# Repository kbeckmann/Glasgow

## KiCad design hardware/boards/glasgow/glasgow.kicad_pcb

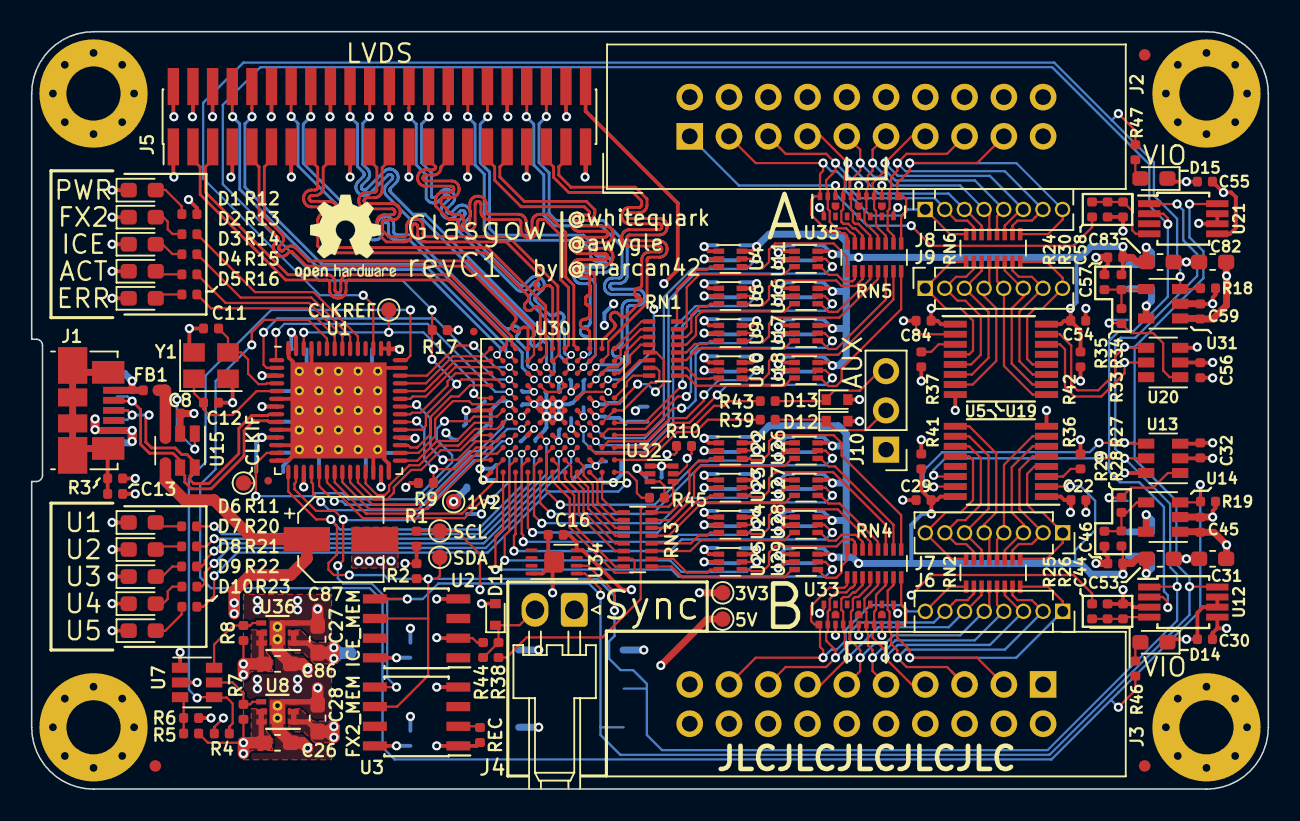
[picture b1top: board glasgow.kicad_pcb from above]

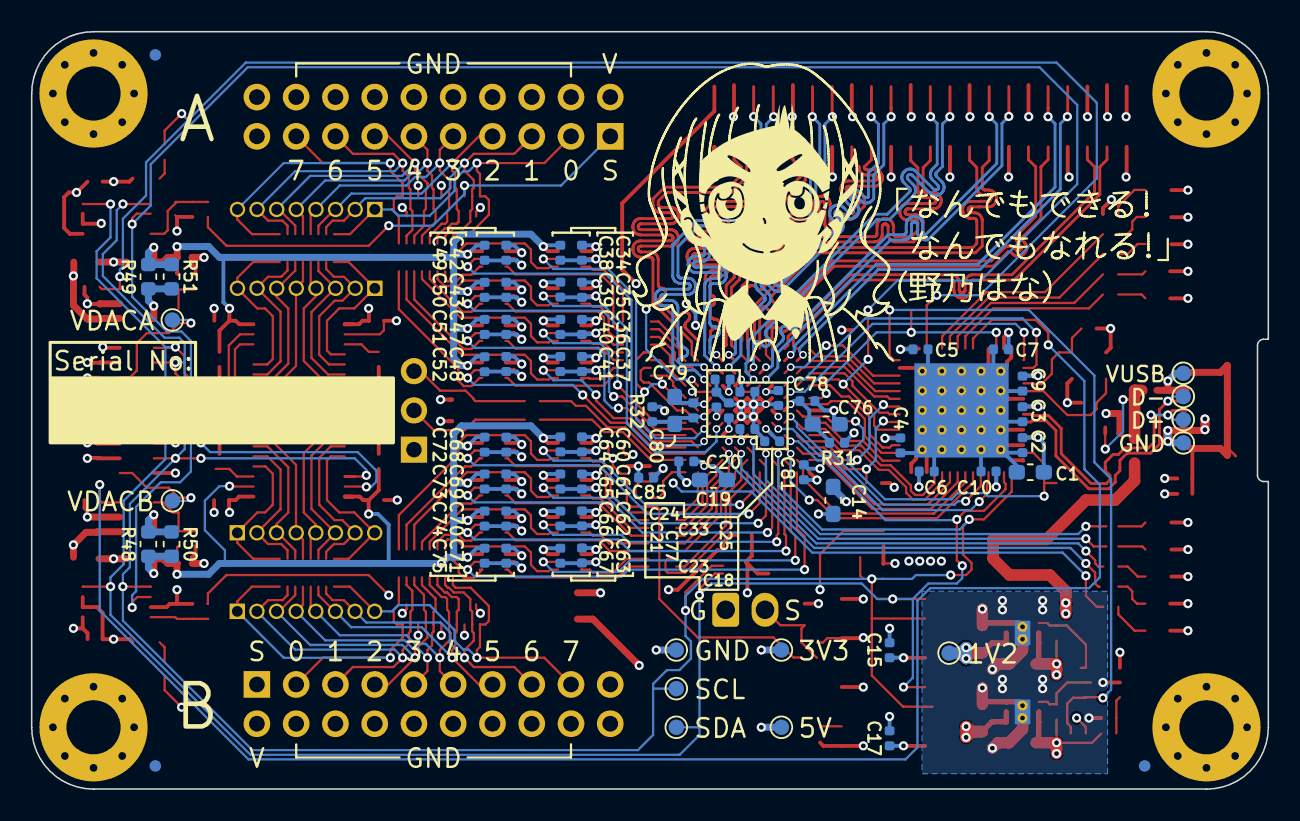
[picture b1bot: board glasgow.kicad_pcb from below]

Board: 4 copper layers, 80.0 x 49.0 mm, 239 parts (81 on the bottom side), 214 nets.

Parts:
C1, C14, C19, C26, C27, C28, C31, C53, C76, C80, C82, C83, C86: 4u7; C_0603_1608Metric_Pad1.05x0.95mm_HandSolder
C2, C3, C4, C5, C6, C7, C8, C9, C10, C13, C15, C16, C17, C18, C20, C21, C22, C23, C24, C25, C29, C30, C32, C33, C34, C35, C36, C37, C38, C39, C40, C41, C42, C43, C45, C46, C47, C48, C49, C50, C51, C52, C54, C55, C56, C57, C59, C60, C61, C62, C63, C64, C65, C66, C67, C68, C69, C70, C71, C72, C73, C74, C75, C77, C78, C79, C81, C84, C85: u1; C_0402_1005Metric
C11, C12: 18p; C_0402_1005Metric
C44, C58: 12n; C_0402_1005Metric
C87: 150u; CP_Elec_5x3.9
D1, D2, D3, D14, D15: GRN; LED_0603_1608Metric_Pad1.05x0.95mm_HandSolder
D4: YEL; LED_0603_1608Metric_Pad1.05x0.95mm_HandSolder
D5: RED; LED_0603_1608Metric_Pad1.05x0.95mm_HandSolder
D6, D10: BLU; LED_0603_1608Metric_Pad1.05x0.95mm_HandSolder
D7, D9: PNK; LED_0603_1608Metric_Pad1.05x0.95mm_HandSolder
D8: WHT; LED_0603_1608Metric_Pad1.05x0.95mm_HandSolder
D11, D12, D13: ESD5Z5.0T1G; D_SOD-523
FB1: Ferrite_Bead; L_0402_1005Metric
FID1, FID2, FID3, FID4, FID5, FID6: Fiducial_0.75mm_Dia_1.5mm_Outer
FID7, FID8: Fiducial_0.5mm_Dia_1mm_Outer
J1: USB_B_Micro; USB_Micro-B_Molex_47346-0001
J2, J3: Conn_02x10_Odd_Even; IDC-Header_2x10_P2.54mm_Vertical
J4: Conn_01x02; Molex_KK-254_1x02_P2.54mm_Horizontal
J5: Conn_02x22_Odd_Even; PinHeader_2x22_P1.27mm_Vertical_SMD
J6, J7, J8, J9: Conn_01x08; PinSocket_1x08_P1.27mm_Vertical
J10: Conn_01x03; PinHeader_1x03_P2.54mm_Vertical
MK1, MK2, MK3, MK4: Mounting_Hole_PAD; MountingHole_3.5mm_Pad_Via_CrtYd
NONO_HANA: MECHOKKU; nono_hana
R1, R2, R15: 2k2; R_0402_1005Metric
R3, R4, R7, R8, R9, R17: 100k; R_0402_1005Metric
R5, R29, R35: 24k3; R_0402_1005Metric
R6, R16, R18, R19, R20, R22, R24, R25, R26, R30, R36, R37, R44: 10k; R_0402_1005Metric
R10, R41, R42: 1k; R_0402_1005Metric
R11, R23: 4k7; R_0402_1005Metric
R12, R13, R14, R46, R47: 20k; R_0402_1005Metric
R21: 6k8; R_0402_1005Metric
R27, R33: 49k9; R_0402_1005Metric
R28, R34: 59k; R_0402_1005Metric
R31, R32: 100; R_0402_1005Metric
R38, R39, R43, R45: 47; R_0402_1005Metric
R40: DNP; R_0402_1005Metric
R48, R49: 0.68; R_0603_1608Metric
R50, R51: DNP; R_0603_1608Metric
RN1, RN3, RN4, RN5: 33; R_Array_Convex_8x0602
RN2, RN6: 10k; R_Array_Convex_8x0602
TP1, TP8: 5V; TestPoint_Pad_D1.0mm
TP2, TP17: 1V2; TestPoint_Pad_D1.0mm
TP3, TP7, TP9: 3V3; TestPoint_Pad_D1.0mm
TP4, TP10: SDA; TestPoint_Pad_D1.0mm
TP5, TP11: SCL; TestPoint_Pad_D1.0mm
TP6: CLKREF; TestPoint_Pad_D1.0mm
TP12: GND; TestPoint_Pad_D1.0mm
TP13: VBUS; TestPoint_Pad_D1.0mm
TP14: USBGND; TestPoint_Pad_D1.0mm
TP15: USBDP; TestPoint_Pad_D1.0mm
TP16: USBDM; TestPoint_Pad_D1.0mm
TP18, TP19: VDAC; TestPoint_Pad_D1.0mm
U1: CY7C68013A-56LTX; Cypress_QFN-56-1EP_8x8mm_P0.5mm_EP6.22x6.22mm_ThermalVias
U2: CAT24M01W; SOIC-8_3.9x4.9mm_P1.27mm
U3: CAT24C256W; SOIC-8_3.9x4.9mm_P1.27mm
U4, U6, U9, U10, U11, U16, U17, U18, U22, U23, U24, U25, U26, U27, U28, U29, U32: SN74LVC1T45DRL; SOT-563
U5, U19: PCA6408APW; TSSOP-16_4.4x5mm_P0.65mm
U7: LM3880MF-1AF; SOT-23-6
U8: TLV75533PDRVR; DFN-6-1EP_2x2mm_P0.65mm_EP1x1.6mm_ThermalVias
U12, U21: ADC081C021CIMM; MSOP-8_3x3mm_P0.65mm
U13, U20: DAC081C081CIMK; SOT-23-6
U14, U31: TPS73101DBV; SOT-23-5
U15: TPD3S014; SOT-23-6
U30: ICE40HX8K-BG121; BGA-121_9.0x9.0mm_Layout11x11_P0.8mm_Ball0.4mm_Pad0.35mm_NS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
U33, U35: MG2040; UDFN-18-3EP_5.5x1.5mm_P0.5mm_EP0.5x0.5mm
U34: ATECC508A; WDFN-8-1EP_3x2mm_P0.5mm_EP1.3x1.4mm
U36: TLV73312PQDRVRQ1; DFN-6-1EP_2x2mm_P0.65mm_EP1x1.6mm_ThermalVias
Y1: 24M; Crystal_SMD_3225-4Pin_3.2x2.5mm

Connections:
+1V2: C14.1, C18.1, C24.1, C25.1, C27.1, C77.1, R31.2, R32.2, TP2.1, TP17.1, U30.D4, U30.D8, U30.H4, U30.H8, U36.1, U36.2
+3V3: C1.1, C2.1, C3.1, C4.1, C5.1, C6.1, C7.1, C9.1, C10.1, C15.1, C16.1, C17.1, C19.1, C20.1, C21.1, C22.1, C23.1, C28.1, C30.1, C32.1, C34.1, C35.1, C36.1, C37.1, C42.1, C43.1, C47.1, C48.1, C55.1, C56.1, C60.1, C61.1, C62.1, C63.1, C68.1, C69.1, C70.1, C71.1, C81.1, C84.1, C85.1, J5.2, R1.2, R2.2, R4.2, R12.1, R17.2, R36.2, R37.2, R40.2, R44.2, TP3.1, TP9.1, U1.3, U1.7, U1.11, U1.17, U1.27, U1.32, U1.43, U1.44, U1.55, U2.2, U2.8, U3.1, U3.8, U4.1, U5.1, U6.1, U8.1, U8.2, U9.1, U10.1, U11.1, U12.5, U13.2, U16.1, U17.1, U18.1, U19.1, U20.2, U21.5, U22.1, U23.1, U24.1, U25.1, U26.1, U27.1, U28.1, U29.1, U30.C10, U30.D6, U30.F8, U30.H6, U30.L11, U32.1, U32.6, U34.8
+5V: C26.2, C31.1, C45.1, C59.1, C82.1, C86.2, C87.1, R5.2, R7.2, R8.2, TP1.1, TP8.1, U7.1, U8.5, U8.6, U14.1, U15.4, U31.1, U36.5, U36.6
/1V2EN: R8.1, U7.6, U36.4
/3V3EN: R7.1, U7.5, U8.4
/A0: U1.37, U30.K3
/A1: U1.38, U30.L2
/CLKIF: TP7.1, U1.13, U30.K6
/CLKREF: TP6.1, U1.54, U30.D5, U30.L5
/D0: U1.18, U30.H7
/D1: U1.19, U30.J7
/D2: U1.20, U30.J9
/D3: U1.21, U30.K10
/D4: U1.22, U30.L10
/D5: U1.23, U30.K9
/D6: U1.24, U30.L8
/D7: U1.25, U30.K7
/ENVA: R18.1, R47.1, U1.45, U31.3
/ENVB: R19.1, R46.1, U1.51, U14.3
/FLAGA: U1.29, U30.L7
/FLAGB: U1.30, U30.K5
/FLAGC: U1.31, U30.L4
/FLAGD: U1.40, U30.J3
/FPGA_DONE: U1.36, U30.K8
/GNDPLL0: C76.2, C78.2, U30.L6
/GNDPLL1: C79.2, C80.2, U30.C5
/IO_Banks/DA0: U4.5, U30.C7
/IO_Banks/DA1: U11.5, U30.C8
/IO_Banks/DA2: U6.5, U30.D7
/IO_Banks/DA3: U16.5, U30.A7
/IO_Banks/DA4: U9.5, U30.B8
/IO_Banks/DA5: U17.5, U30.A8
/IO_Banks/DA6: U10.5, U30.B9
/IO_Banks/DA7: U18.5, U30.A9
/IO_Banks/DB0: U22.5, U30.F9
/IO_Banks/DB1: U26.5, U30.G11
/IO_Banks/DB2: U23.5, U30.G10
/IO_Banks/DB3: U27.5, U30.H11
/IO_Banks/DB4: U24.5, U30.H10
/IO_Banks/DB5: U28.5, U30.J11
/IO_Banks/DB6: U25.5, U30.J10
/IO_Banks/DB7: U29.5, U30.K11
/IO_Banks/IO_Buffer_A/VFB: R33.2, R34.1, R35.2, U31.4
/IO_Banks/IO_Buffer_A/VSAMP: C58.1, R24.1, R30.2, U21.4
/IO_Banks/IO_Buffer_A/VSENSE: J2.1, R24.2, U35.9
/IO_Banks/IO_Buffer_A/Y0: RN5.1, U4.4
/IO_Banks/IO_Buffer_A/Y1: RN5.2, U11.4
/IO_Banks/IO_Buffer_A/Y2: RN5.3, U6.4
/IO_Banks/IO_Buffer_A/Y3: RN5.4, U16.4
/IO_Banks/IO_Buffer_A/Y4: RN5.5, U9.4
/IO_Banks/IO_Buffer_A/Y5: RN5.6, U17.4
/IO_Banks/IO_Buffer_A/Y6: RN5.7, U10.4
/IO_Banks/IO_Buffer_A/Y7: RN5.8, U18.4
/IO_Banks/IO_Buffer_A/Z0: J2.3, J8.1, RN5.16, RN6.8, U35.11
/IO_Banks/IO_Buffer_A/Z1: J2.5, J8.2, RN5.15, RN6.7, U35.10
/IO_Banks/IO_Buffer_A/Z2: J2.7, J8.3, RN5.14, RN6.6, U35.8
/IO_Banks/IO_Buffer_A/Z3: J2.9, J8.4, RN5.13, RN6.5, U35.7
/IO_Banks/IO_Buffer_A/Z4: J2.11, J8.5, RN5.12, RN6.4, U35.5
/IO_Banks/IO_Buffer_A/Z5: J2.13, J8.6, RN5.11, RN6.3, U35.4
/IO_Banks/IO_Buffer_A/Z6: J2.15, J8.7, RN5.10, RN6.2, U35.2
/IO_Banks/IO_Buffer_A/Z7: J2.17, J8.8, RN5.9, RN6.1, U35.1
/IO_Banks/IO_Buffer_B/VFB: R27.2, R28.1, R29.2, U14.4
/IO_Banks/IO_Buffer_B/VSAMP: C44.1, R25.1, R26.2, U12.4
/IO_Banks/IO_Buffer_B/VSENSE: J3.1, R25.2, U33.9
/IO_Banks/IO_Buffer_B/Y0: RN4.1, U22.4
/IO_Banks/IO_Buffer_B/Y1: RN4.2, U26.4
/IO_Banks/IO_Buffer_B/Y2: RN4.3, U23.4
/IO_Banks/IO_Buffer_B/Y3: RN4.4, U27.4
/IO_Banks/IO_Buffer_B/Y4: RN4.5, U24.4
/IO_Banks/IO_Buffer_B/Y5: RN4.6, U28.4
/IO_Banks/IO_Buffer_B/Y6: RN4.7, U25.4
/IO_Banks/IO_Buffer_B/Y7: RN4.8, U29.4
/IO_Banks/IO_Buffer_B/Z0: J3.3, J6.1, RN2.8, RN4.16, U33.11
/IO_Banks/IO_Buffer_B/Z1: J3.5, J6.2, RN2.7, RN4.15, U33.10
/IO_Banks/IO_Buffer_B/Z2: J3.7, J6.3, RN2.6, RN4.14, U33.8
/IO_Banks/IO_Buffer_B/Z3: J3.9, J6.4, RN2.5, RN4.13, U33.7
/IO_Banks/IO_Buffer_B/Z4: J3.11, J6.5, RN2.4, RN4.12, U33.5
/IO_Banks/IO_Buffer_B/Z5: J3.13, J6.6, RN2.3, RN4.11, U33.4
/IO_Banks/IO_Buffer_B/Z6: J3.15, J6.7, RN2.2, RN4.10, U33.2
/IO_Banks/IO_Buffer_B/Z7: J3.17, J6.8, RN2.1, RN4.9, U33.1
/IO_Banks/QA0: RN1.1, U30.A1
/IO_Banks/QA1: RN1.2, U30.A2
/IO_Banks/QA2: RN1.3, U30.B3
/IO_Banks/QA3: RN1.4, U30.A3
/IO_Banks/QA4: RN1.5, U30.B5, U30.B6
/IO_Banks/QA5: RN1.6, U30.A4
/IO_Banks/QA6: RN1.7, U30.A6, U30.B7
/IO_Banks/QA7: RN1.8, U30.A5
/IO_Banks/QB0: RN3.1, U30.B11
/IO_Banks/QB1: RN3.2, U30.C11
/IO_Banks/QB2: RN3.3, U30.D10
/IO_Banks/QB3: RN3.4, U30.D11
/IO_Banks/QB4: RN3.5, U30.E10
/IO_Banks/QB5: RN3.6, U30.E11
/IO_Banks/QB6: RN3.7, U30.F11
/IO_Banks/QB7: RN3.8, U30.F10
/IO_Banks/U1: R11.1, U30.G9
/IO_Banks/U2: R20.1, U30.G8
/IO_Banks/U3: R21.1, U30.E9
/IO_Banks/U4: R22.1, U30.D9
/IO_Banks/U5: R23.1, U30.E8
/IO_Banks/VIOA: C38.1, C39.1, C40.1, C41.1, C49.1, C50.1, C51.1, C52.1, C54.1, C57.1, C83.1, J2.2, R34.2, R42.2, R49.2, R51.2, U4.6, U6.6, U9.6, U10.6, U11.6, U16.6, U17.6, U18.6, U19.16, U35.3, U35.6
/IO_Banks/VIOB: C29.1, C46.1, C53.1, C64.1, C65.1, C66.1, C67.1, C72.1, C73.1, C74.1, C75.1, J3.2, R28.2, R41.2, R48.2, R50.2, U5.2, U5.16, U22.6, U23.6, U24.6, U25.6, U26.6, U27.6, U28.6, U29.6, U33.3, U33.6
/IO_Banks/VIO_AUX: C33.1, J5.44, U30.E4, U30.G4
/IO_Banks/Z0_N: J5.41, U30.B2
/IO_Banks/Z0_P: J5.39, U30.B1
/IO_Banks/Z1_N: J5.38, U30.C3
/IO_Banks/Z1_P: J5.40, U30.C4
/IO_Banks/Z2_N: J5.33, U30.C1
/IO_Banks/Z2_P: J5.35, U30.C2
/IO_Banks/Z3_N: J5.29, U30.D1
/IO_Banks/Z3_P: J5.27, U30.E1
/IO_Banks/Z4_N: J5.34, U30.D3
/IO_Banks/Z4_P: J5.32, U30.D2
/IO_Banks/Z5_N: J5.26, U30.E3
/IO_Banks/Z5_P: J5.28, U30.E2
/IO_Banks/Z6_N: J5.23, U30.F2
/IO_Banks/Z6_P: J5.21, U30.F1
/IO_Banks/Z7_N: J5.20, U30.F3
/IO_Banks/Z7_P: J5.22, U30.F4
/IO_Banks/Z8_N: J5.17, U30.G2
/IO_Banks/Z8_P: J5.15, U30.G1
/IO_Banks/Z9_N: J5.14, U30.H3
/IO_Banks/Z9_P: J5.16, U30.G3
/IO_Banks/Z10_N: J5.11, U30.H2
/IO_Banks/Z10_P: J5.9, U30.H1
/IO_Banks/Z11_N: J5.3, U30.K1
/IO_Banks/Z11_P: J5.5, U30.J1
/IO_Banks/Z12_N: J5.10, U30.J2
/IO_Banks/Z12_P: J5.8, U30.K2
/IO_Banks/~SYNC: D11.1, J4.2, R38.1, R44.1
/LED_ACT: R15.1, U1.49
/LED_CY: R13.1, U1.47
/LED_ERR: R16.1, U1.50
/LED_FPGA: R14.1, U1.48
/OE: U1.35, U30.L3
/PGOOD: R5.1, R6.2, U7.3
/PKTEND: U1.39, U30.L1
/RD: U1.1, U30.J5
/SCL: R2.1, TP5.1, TP11.1, U1.15, U2.6, U3.6, U5.14, U12.1, U13.5, U19.14, U20.5, U21.1, U30.H9, U34.6
/SDA: R1.1, TP4.1, TP10.1, U1.16, U2.5, U3.5, U5.15, U12.8, U13.4, U19.15, U20.4, U21.8, U30.J8, U34.5
/SHLD: C13.1, J1.6, R3.1
/USB_N: J1.2, TP16.1, U1.9, U15.5
/USB_P: J1.3, TP15.1, U1.8, U15.6
/VCCPLL0: C76.1, C78.1, R31.1, U30.J6
/VCCPLL1: C79.1, C80.1, R32.1, U30.C6
/VUSB: C8.1, FB1.2, U15.1, U15.3
/WR: U1.2, U30.J4
/XTALIN: C12.1, U1.5, Y1.1
/XTALOUT: C11.1, U1.4, Y1.3
/~ALERT: R17.1, U1.33, U12.2, U21.2, U30.K4
/~CY_RESET: R4.1, U1.42, U7.4
/~FPGA_RESET: R9.2, U1.34, U30.L9
GND: C1.2, C2.2, C3.2, C4.2, C5.2, C6.2, C7.2, C8.2, C9.2, C10.2, C11.2, C12.2, C13.2, C14.2, C15.2, C16.2, C17.2, C18.2, C19.2, C20.2, C21.2, C22.2, C23.2, C24.2, C25.2, C26.1, C27.2, C28.2, C29.2, C30.2, C31.2, C32.2, C33.2, C34.2, C35.2, C36.2, C37.2, C38.2, C39.2, C40.2, C41.2, C42.2, C43.2, C44.2, C45.2, C46.2, C47.2, C48.2, C49.2, C50.2, C51.2, C52.2, C53.2, C54.2, C55.2, C56.2, C57.2, C58.2, C59.2, C60.2, C61.2, C62.2, C63.2, C64.2, C65.2, C66.2, C67.2, C68.2, C69.2, C70.2, C71.2, C72.2, C73.2, C74.2, C75.2, C77.2, C81.2, C82.2, C83.2, C84.2, C85.2, C86.1, C87.2, D1.1, D2.1, D3.1, D4.1, D5.1, D6.1, D7.1, D8.1, D9.1, D10.1, D11.2, D12.2, D13.2, D14.1, D15.1, J1.5, J2.4, J2.6, J2.8, J2.10, J2.12, J2.14, J2.16, J2.18, J3.4, J3.6, J3.8, J3.10, J3.12, J3.14, J3.16, J3.18, J4.1, J5.1, J5.4, J5.6, J5.7, J5.12, J5.13, J5.18, J5.19, J5.24, J5.25, J5.30, J5.31, J5.36, J5.37, J5.42, J5.43, J10.1, MK1.1, MK2.1, MK3.1, MK4.1, R3.2, R6.1, R9.1, R10.2, R18.2, R19.2, R26.1, R29.1, R30.1, R35.1, R41.1, R42.1, TP12.1, TP14.1, U1.6, U1.10, U1.12, U1.14, U1.26, U1.28, U1.41, U1.53, U1.56, U1.57, U2.4, U3.4, U4.2, U5.8, U6.2, U7.2, U8.3, U8.7, U9.2, U10.2, U11.2, U12.3, U12.6, U12.7, U13.3, U13.6, U14.2, U15.2, U16.2, U17.2, U18.2, U19.2, U19.8, U20.3, U21.6, U21.7, U22.2, U23.2, U24.2, U25.2, U26.2, U27.2, U28.2, U29.2, U30.E5, U30.E6, U30.E7, U30.F5, U30.F6, U30.F7, U30.G5, U30.G6, U30.G7, U30.H5, U31.2, U32.2, U33.12, U33.18, U34.4, U34.9, U35.12, U35.18, U36.3, U36.7, Y1.2, Y1.4
unnamed: D1.2, R12.2
unnamed: D2.2, R13.2
unnamed: D3.2, R14.2
unnamed: D4.2, R15.2
unnamed: D5.2, R16.2
unnamed: D6.2, R11.2
unnamed: D7.2, R20.2
unnamed: D8.2, R21.2
unnamed: D9.2, R22.2
unnamed: D10.2, R23.2
unnamed: D12.1, J10.2, R39.1
unnamed: D13.1, J10.3, R43.1
unnamed: D14.2, R46.2
unnamed: D15.2, R47.2
unnamed: FB1.1, J1.1, TP13.1
unnamed: J7.1, RN2.9, U5.4
unnamed: J7.2, RN2.10, U5.5
unnamed: J7.3, RN2.11, U5.6
unnamed: J7.4, RN2.12, U5.7
unnamed: J7.5, RN2.13, U5.9
unnamed: J7.6, RN2.14, U5.10
unnamed: J7.7, RN2.15, U5.11
unnamed: J7.8, RN2.16, U5.12
unnamed: J9.1, RN6.9, U19.4
unnamed: J9.2, RN6.10, U19.5
unnamed: J9.3, RN6.11, U19.6
unnamed: J9.4, RN6.12, U19.7
unnamed: J9.5, RN6.13, U19.9
unnamed: J9.6, RN6.14, U19.10
unnamed: J9.7, RN6.15, U19.11
unnamed: J9.8, RN6.16, U19.12
unnamed: R10.1, U30.B4, U32.5
unnamed: R27.1, TP18.1, U13.1
unnamed: R33.1, TP19.1, U20.1
unnamed: R36.1, U5.3
unnamed: R37.1, U19.3
unnamed: R38.2, U32.4
unnamed: R39.2, U30.A10
unnamed: R40.1, U3.2
unnamed: R43.2, U30.C9
unnamed: R45.1, U32.3
unnamed: R45.2, U30.A11
unnamed: R48.1, R50.1, U14.5
unnamed: R49.1, R51.1, U31.5
unnamed: RN1.9, U18.3
unnamed: RN1.10, U10.3
unnamed: RN1.11, U17.3
unnamed: RN1.12, U9.3
unnamed: RN1.13, U16.3
unnamed: RN1.14, U6.3
unnamed: RN1.15, U11.3
unnamed: RN1.16, U4.3
unnamed: RN3.9, U29.3
unnamed: RN3.10, U25.3
unnamed: RN3.11, U28.3
unnamed: RN3.12, U24.3
unnamed: RN3.13, U27.3
unnamed: RN3.14, U23.3
unnamed: RN3.15, U26.3
unnamed: RN3.16, U22.3

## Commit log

2018-10-29 Initial Rev C IO cell schematic.
2018-10-29 Add modified SOT-563 footprint
2018-10-29 Update fp-lib-table for SOT-563 lib directory
2018-10-29 revC WIP PCB work
2018-10-31 revC: FX2<->FPGA routing take 1
2018-10-31 revC: FX2<->FPGA routing take 2
2018-10-31 revC: delete old FPGA
    No useful information left, since it's mostly just the port routing
    remaining
2018-10-31 revC: route missing D0 and D1
2018-10-31 revC: fix some misc DRC errors
2018-10-31 revC: Update SOT563 footprints to Glasgow version and more DRC fixes
2018-10-31 revC: fix connector placement, LVDS connector testing
2018-10-31 revC: route LVDS
2018-11-22 ws2812b: Initial commit
    It actually works, wtf?
    Broke everything
    Works pretty well now
    Hacky script
    16 bit size header
    Better effect
2018-12-16 Move applet
2018-12-16 move file
2018-12-16 Works again..
2018-12-16 Works great with 2 datapins
2018-12-16 Improve performance
2018-12-16 Works perfectly now
2018-12-16 Add tool
2018-12-16 Commit scripts
2018-12-16 Fix the video script
2018-12-26 vendor firmware
2019-07-28 logger
2020-05-14 Add ugly udp datalogger
2020-05-21 refilled zones and revC1 jlc
